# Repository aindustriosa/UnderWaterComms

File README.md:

# UnderWaterComms
UnderWater ultrasonic communications project

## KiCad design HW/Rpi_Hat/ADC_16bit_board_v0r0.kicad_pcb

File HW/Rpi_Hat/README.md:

Raspberry Pi Hat including:
- ADS8685IPWR ADC
- MAX98357A DAC

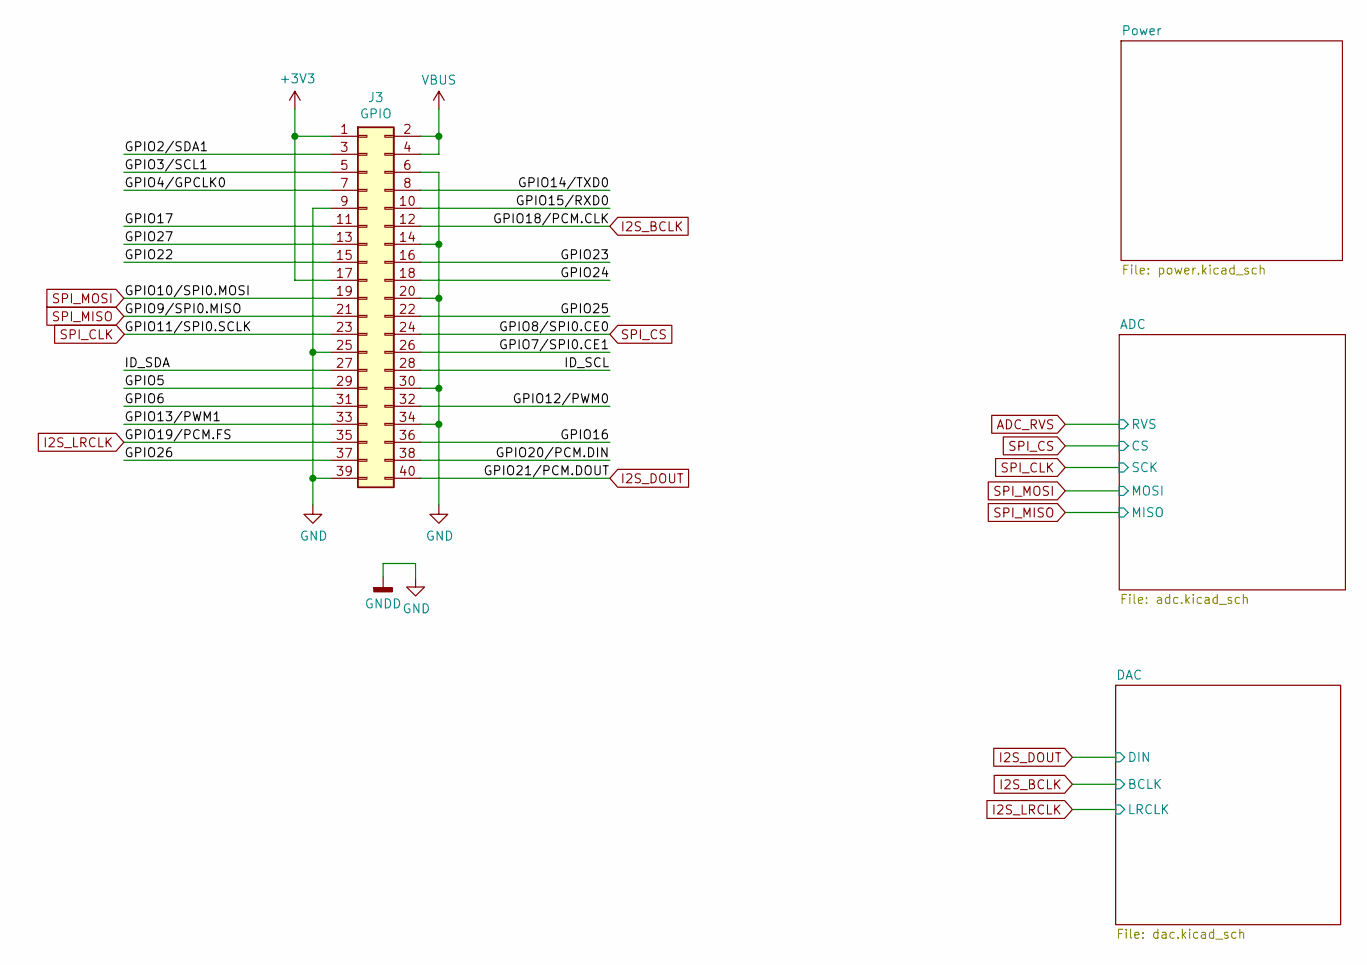
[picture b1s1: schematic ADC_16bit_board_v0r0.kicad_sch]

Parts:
J3: GPIO; PinSocket_2x20_P2.54mm_Vertical; Digi-Key_PN 732-61304021821-ND

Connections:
+3V3: J3.1, J3.17
/GPIO2/SDA1: J3.3
/GPIO3/SCL1: J3.5
/GPIO4/GPCLK0: J3.7
/GPIO5: J3.29
/GPIO6: J3.31
/GPIO7/SPI0.CE1: J3.26
/GPIO12/PWM0: J3.32
/GPIO13/PWM1: J3.33
/GPIO14/TXD0: J3.8
/GPIO15/RXD0: J3.10
/GPIO16: J3.36
/GPIO17: J3.11
/GPIO20/PCM.DIN: J3.38
/GPIO22: J3.15
/GPIO23: J3.16
/GPIO24: J3.18
/GPIO25: J3.22
/GPIO26: J3.37
/GPIO27: J3.13
/ID_SCL: J3.28
/ID_SDA: J3.27
GND: J3.6, J3.9, J3.14, J3.20, J3.25, J3.30, J3.34, J3.39; also elsewhere on the board
I2S_BCLK: J3.12; also elsewhere on the board
I2S_DOUT: J3.40; also elsewhere on the board
I2S_LRCLK: J3.35; also elsewhere on the board
SPI_CLK: J3.23; also elsewhere on the board
SPI_CS: J3.24; also elsewhere on the board
SPI_MISO: J3.21; also elsewhere on the board
SPI_MOSI: J3.19; also elsewhere on the board
VBUS: J3.2, J3.4; also elsewhere on the board

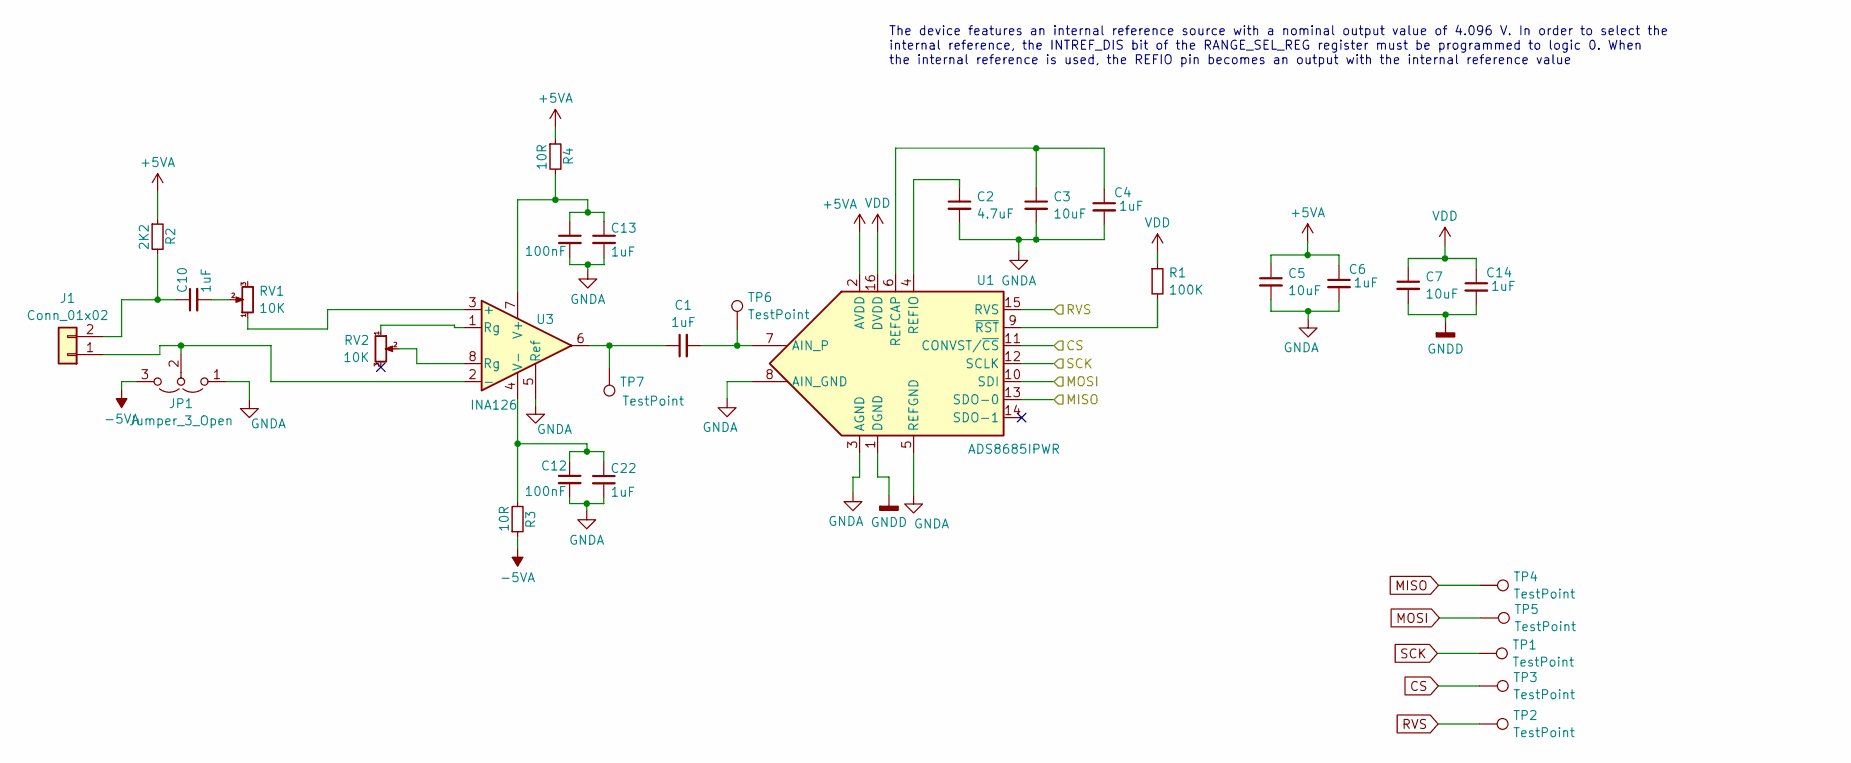
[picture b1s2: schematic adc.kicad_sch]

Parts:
C1, C4, C6, C10, C13, C14, C22: 1uF; C_0603_1608Metric; Digi-Key_PN 1276-1019-1-ND
C2: 4.7uF; C_0603_1608Metric; Digi-Key_PN 1276-1784-1-ND
C3, C5, C7: 10uF; C_0603_1608Metric; Digi-Key_PN 1276-1869-1-ND
C11, C12: 100nF; C_0603_1608Metric; Digi-Key_PN 1276-1000-1-ND
J1: Conn_01x02; TerminalBlock_Phoenix_PT-1,5-2-3.5-H_1x02_P3.50mm_Horizontal; Digi-Key_PN 277-1721-ND
JP1: Jumper_3_Open; SolderJumper-3_P1.3mm_Open_RoundedPad1.0x1.5mm
R1: 100K; R_0603_1608Metric; Digi-Key_PN RMCF0603FT100KCT-ND
R2: 2K2; R_0603_1608Metric; Digi-Key_PN P2.2KGCT-ND
R3, R4: 10R; R_0603_1608Metric; Digi-Key_PN RMCF0603FT10R0CT-ND
RV1, RV2: 10K; TRIM_PV37W103C01B00; Digi-Key_PN 490-2970-ND
TP1, TP2, TP3, TP4, TP5, TP6, TP7: TestPoint; TestPoint_Pad_2.0x2.0mm
U1: ADS8685IPWR; TSSOP-16_4.4x5mm_P0.65mm; Digi-Key_PN 296-48485-1-ND
U3: INA126; SOIC-8_3.9x4.9mm_P1.27mm; Digi-Key_PN 296-38946-1-ND

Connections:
+5VA: C5.1, C6.1, R2.1, R4.1, U1.2 (AVDD); also elsewhere on the board
-5VA: JP1.3 (B), R3.1; also elsewhere on the board
ADC_RVS: TP2.1, U1.15 (RVS)
GND: C7.2, C14.2, U1.1 (DGND); also elsewhere on the board
GNDA: C2.2, C3.2, C4.2, C5.2, C6.2, C11.2, C12.2, C13.2, C22.2, JP1.1 (A), U1.3 (AGND), U1.5 (REFGND), U1.8 (AIN_GND), U3.5 (Ref); also elsewhere on the board
unnamed: C1.1, TP7.1, U3.6
unnamed: C10.2, RV1.2
unnamed: J1.1, JP1.2 (C), U3.2 (-)
unnamed: C10.1, J1.2, R2.2
unnamed: RV2.1, U3.1 (Rg)
unnamed: RV2.2, U3.8 (Rg)
unnamed: C1.2, TP6.1, U1.7 (AIN_P)
unnamed: C3.1, C4.1, U1.6 (REFCAP)
unnamed: C2.1, U1.4 (REFIO)
unnamed: R1.2, U1.9 (~RST)
unnamed: RV1.1, U3.3 (+)
unnamed: C11.1, C13.1, R4.2, U3.7 (V+)
unnamed: C12.1, C22.1, R3.2, U3.4 (V-)
SPI_CLK: TP1.1, U1.12 (SCLK); also elsewhere on the board
SPI_CS: TP3.1, U1.11 (CONVST/~CS); also elsewhere on the board
SPI_MISO: TP4.1, U1.13 (SDO-0); also elsewhere on the board
SPI_MOSI: TP5.1, U1.10 (SDI); also elsewhere on the board
VDD: C7.1, C14.1, R1.1, U1.16 (DVDD); also elsewhere on the board

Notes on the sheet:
The device features an internal reference source with a nominal output value of 4.096 V. In order to select the internal reference, the INTREF_DIS bit of the RANGE_SEL_REG register must be programmed to logic 0. When the internal reference is used, the REFIO pin becomes an output with the internal 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

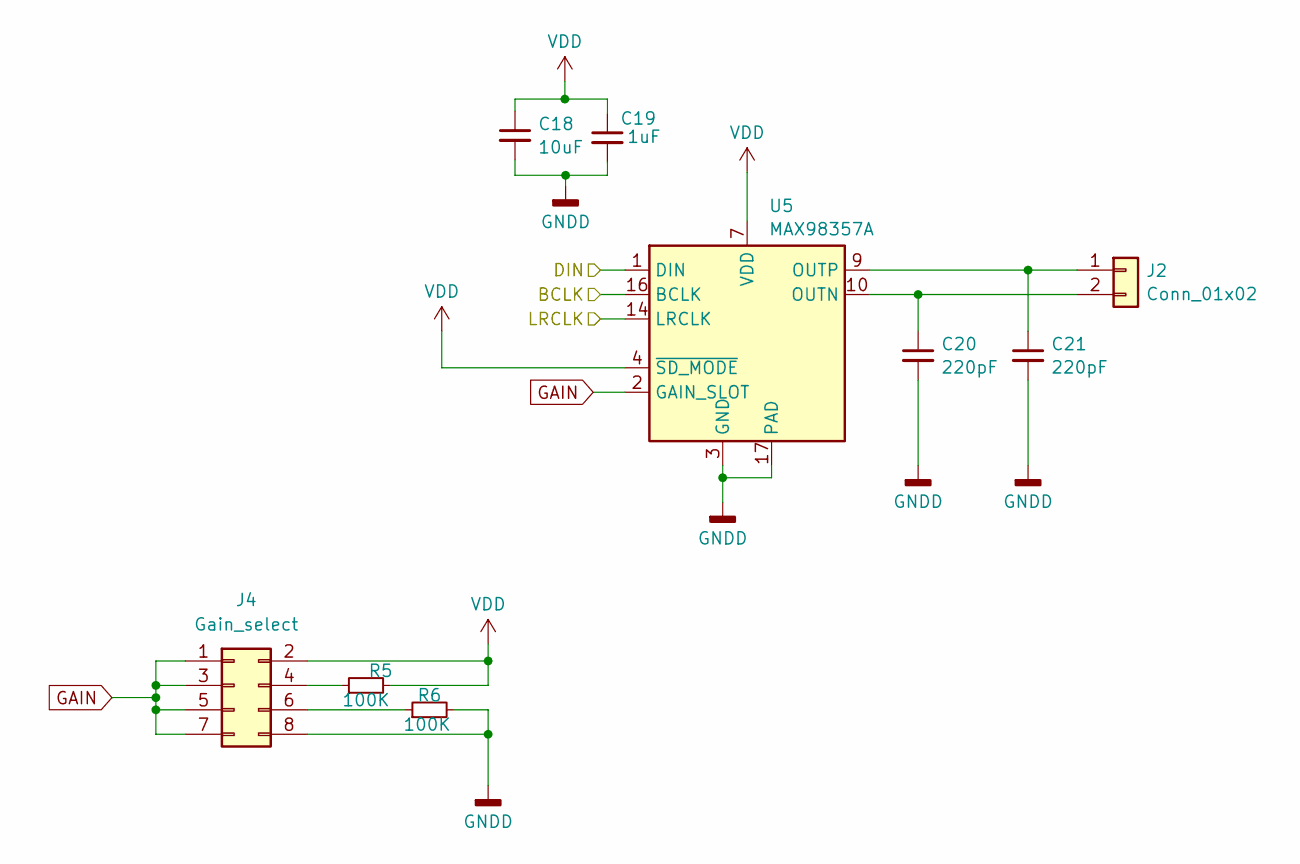
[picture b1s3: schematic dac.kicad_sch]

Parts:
C18: 10uF; C_0603_1608Metric; Digi-Key_PN 1276-1869-1-ND
C19: 1uF; C_0603_1608Metric; Digi-Key_PN 1276-1019-1-ND
C20, C21: 220pF; C_0603_1608Metric; Digi-Key_PN 1276-1986-1-ND
J2: Conn_01x02; TerminalBlock_Phoenix_PT-1,5-2-3.5-H_1x02_P3.50mm_Horizontal; Digi-Key_PN 277-1721-ND
J4: Gain_select; PinHeader_2x04_P2.54mm_Vertical; Digi-Key_PN 2057-PH2-08-UA-ND
R5, R6: 100K; R_0603_1608Metric; Digi-Key_PN RMCF0603FT100KCT-ND
U5: MAX98357A; TQFN-16-1EP_3x3mm_P0.5mm_EP1.23x1.23mm; Digi-Key_PN MAX98357AETE+TCT-ND

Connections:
GAIN: J4.1, J4.3, J4.5, J4.7, U5.2 (GAIN_SLOT)
GND: C18.2, C19.2, C20.2, C21.2, J4.8, R6.2, U5.3 (GND), U5.11 (GND), U5.15 (GND), U5.17 (PAD); also elsewhere on the board
I2S_BCLK: U5.16 (BCLK); also elsewhere on the board
I2S_DOUT: U5.1 (DIN); also elsewhere on the board
I2S_LRCLK: U5.14 (LRCLK); also elsewhere on the board
unnamed: C21.1, J2.1, U5.9 (OUTP)
unnamed: C20.1, J2.2, U5.10 (OUTN)
unnamed: J4.4, R5.1
unnamed: J4.6, R6.1
VDD: C18.1, C19.1, J4.2, R5.2, U5.4 (~SD_MODE), U5.7 (VDD), U5.8 (VDD); also elsewhere on the board

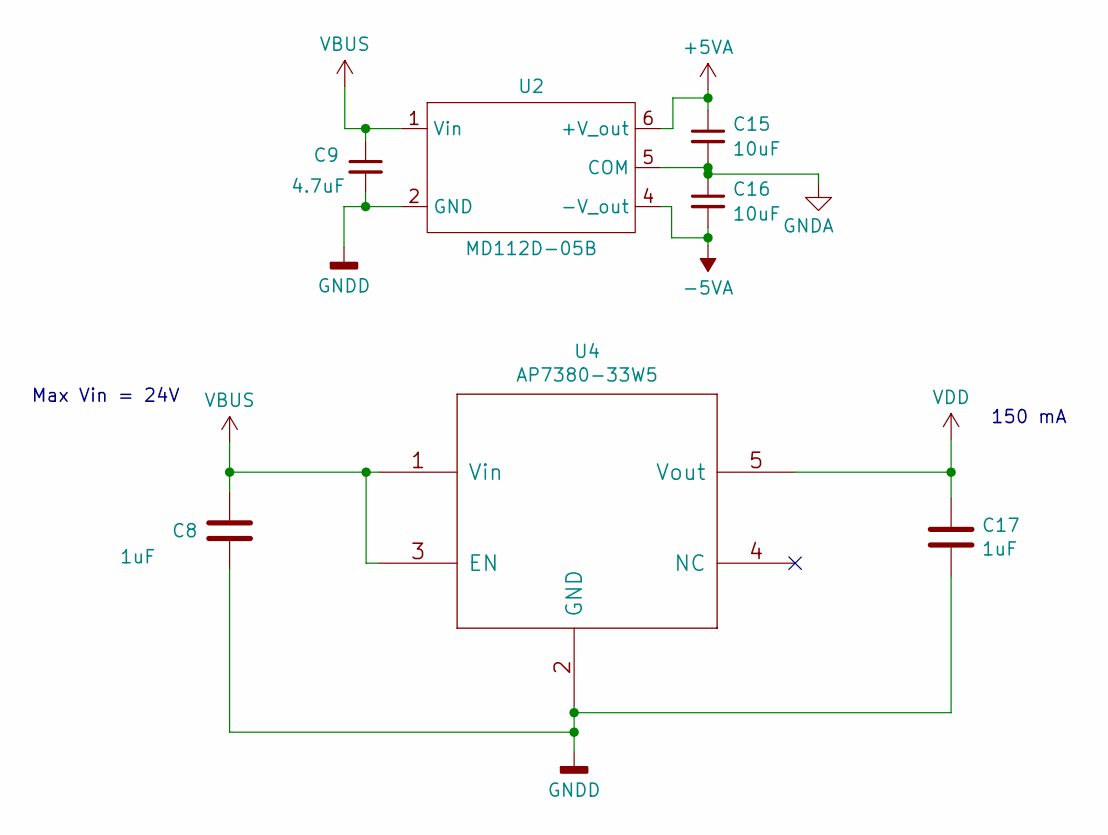
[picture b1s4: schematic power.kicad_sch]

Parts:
C8, C17: 1uF; C_0603_1608Metric; Digi-Key_PN 1276-1019-1-ND
C9: 4.7uF; C_0603_1608Metric; Digi-Key_PN 1276-1784-1-ND
C15, C16: 10uF; C_0603_1608Metric; Digi-Key_PN 1276-1869-1-ND
U2: MD112D-05B; Converter_DCDC_TRACO_TBA1-xxxxE_Dual_THT; Digi-Key_PN 5943-MD112D-05B-ND
U4: AP7380-33W5; SOT-23-5; Digi-Key_PN AP7380-33W5-7DICT-ND

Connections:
+5VA: C15.1, U2.6 (+V_out); also elsewhere on the board
-5VA: C16.2, U2.4 (-V_out); also elsewhere on the board
GND: C8.2, C9.2, C17.2, U2.2 (GND), U4.2 (GND); also elsewhere on the board
GNDA: C15.2, C16.1, U2.5 (COM); also elsewhere on the board
VBUS: C8.1, C9.1, U2.1 (Vin), U4.1 (Vin), U4.3 (EN); also elsewhere on the board
VDD: C17.1, U4.5 (Vout); also elsewhere on the board

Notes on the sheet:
Max Vin = 24V
150 mA

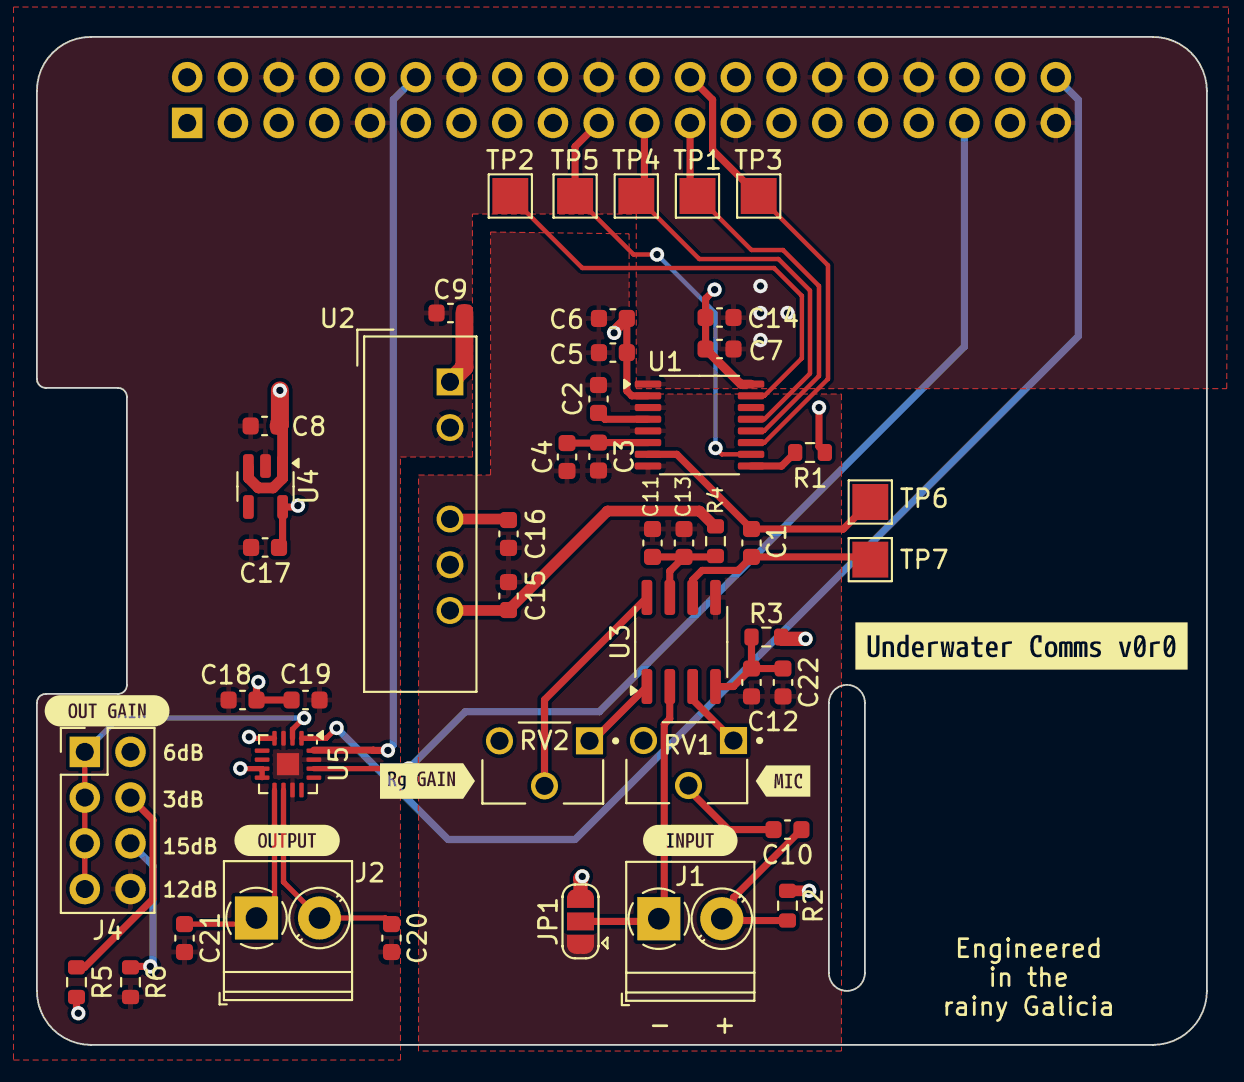
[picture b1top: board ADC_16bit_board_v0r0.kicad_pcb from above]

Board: 4 copper layers, 65.0 x 56.0 mm, 53 parts (1 on the bottom side), 33 nets.

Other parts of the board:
kibuzzard-67B85FF2: G***; kibuzzard-67B85FF2
kibuzzard-67B869D1: G***; kibuzzard-67B869D1
kibuzzard-67B86721: G***; kibuzzard-67B86721
kibuzzard-67BC9731: G***; kibuzzard-67BC9731
kibuzzard-67BC9758: G***; kibuzzard-67BC9758
kibuzzard-67BD956C: G***; kibuzzard-67BD956C

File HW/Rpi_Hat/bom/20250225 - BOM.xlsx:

References | Value | Footprint | Digi-Key_PN | Quantity |  | 2 units
C1, C4, C6, C8, C10, C13, C14, C17, C19, C22 | 1uF | C_0603_1608Metric | 1276-1019-1-ND | 10 |  | 20 | 1276-1019-1-ND
C3, C5, C7, C15, C16, C18 | 10uF | C_0603_1608Metric | 1276-1869-1-ND | 6 |  | 12 | 1276-1869-1-ND
C2, C9 | 4.7uF | C_0603_1608Metric | 1276-1784-1-ND | 2 |  | 4 | 1276-1784-1-ND
C11, C12 | 100nF | C_0603_1608Metric | 1276-1000-1-ND | 2 |  | 4 | 1276-1000-1-ND
C20, C21 | 220pF | C_0603_1608Metric | 1276-1986-1-ND | 2 |  | 4 | 1276-1986-1-ND
R1, R5, R6 | 100K | R_0603_1608Metric | RMCF0603FT100KCT-ND | 3 |  | 6 | RMCF0603FT100KCT-ND
R3, R4 | 10R | R_0603_1608Metric | RMCF0603FT10R0CT-ND | 2 |  | 4 | RMCF0603FT10R0CT-ND
R2 | 2K2 | R_0603_1608Metric | P2.2KGCT-ND | 1 |  | 2 | P2.2KGCT-ND
U1 | ADS8685IPWR | TSSOP-16_4.4x5mm_P0.65mm | 296-48485-1-ND | 1 |  | 2 | 296-48485-1-ND
U2 | MD112D-05B | Converter_DCDC_TRACO_TBA1-xxxxE_Dual_THT | 5943-MD112D-05B-ND | 1 |  | 2 | 5943-MD112D-05B-ND
U3 | INA126 | SOIC-8_3.9x4.9mm_P1.27mm | 296-38946-1-ND | 1 |  | 2 | 296-38946-1-ND
U4 | AP7380-33W5 | SOT-23-5 | AP7380-33W5-7DICT-ND | 1 |  | 2 | AP7380-33W5-7DICT-ND
U5 | MAX98357A | TQFN-16-1EP_3x3mm_P0.5mm_EP1.23x1.23mm | MAX98357AETE+TCT-ND | 1 |  | 2 | MAX98357AETE+TCT-ND
TP1, TP2, TP3, TP4, TP5, TP6, TP7 | TestPoint | TestPoint_Pad_2.0x2.0mm |  | 7
RV1, RV2 | 10K | TRIM_PV37W103C01B00 | 490-2970-ND | 2 |  | 4 | 490-2970-ND
J1, J2 | Conn_01x02 | TerminalBlock_Phoenix_PT-1,5-2-3.5-H_1x02_P3.50mm_Horizontal | 277-1721-ND | 2 |  | 4 | 277-1721-ND
J3 | GPIO | PinSocket_2x20_P2.54mm_Vertical | 732-61304021821-ND | 1 |  | 2 | 732-61304021821-ND
J4 | Gain_select | PinHeader_2x04_P2.54mm_Vertical | 2057-PH2-08-UA-ND | 1 |  | 2 | 2057-PH2-08-UA-ND

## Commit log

2025-02-27 Create README.md
    Initial commit
2025-02-27 First PCB design
